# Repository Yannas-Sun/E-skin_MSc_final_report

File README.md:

# E-SKIN MSc final report companion

This repository is the evidence package for a modular electronic-skin prototype and its final MSc report. It collects the report-linked experimental records, derived analyses, hardware design evidence and selected figures needed to assess the reported communication, power and calibration results.

## Contents

- [Final report PDF](main_final.pdf)
- [Project background](#project-background)
- [System and data path](#system-and-data-path)
- [Hardware overview](#hardware-overview)
- [Core reported results](#core-reported-results)
- [Repository structure](#repository-structure)
- [Software simulation](#software-simulation)
- [Evidence and reproduction](#evidence-and-reproduction)
- [Scope limits](#scope-limits)

## Project background

The final report treats the E-SKIN prototype as a system-level scalability problem. It starts from an existing modular FSR platform and evaluates whether adding sensing modules remains practical across the complete chain: local acquisition, shared communication, host transport, power delivery and calibration.

### Research gap

Existing e-skin work often foregrounds sensing materials, array geometry or local sensor performance. The report identifies a system-level gap: the available modular prototype had not been evaluated as one connected scaling problem across data traffic, regulated power and calibration repeatability. In particular, the report needed evidence for:

- whether complete FSR data can be transported as modules are added, and whether cached change-driven DELTA frames reduce the same-rate traffic;
- whether the parallel 3.3 V supply maintains the specified voltage range as module count increases, without confusing static readings with a verified transient capacity; and
- whether a layer-wide calibration workflow reduces cell-to-cell variation and reconstructs applied whole-layer mass for separately calibrated FSR layers.

The report separates measured behaviour for N = 1–4 modules from conditional model projections beyond the measured range. The repository follows the same boundary.

### Hypotheses to be tested

The report defines the following hypotheses in its Background chapter. They are listed here as the claims the evidence package is intended to test or bound.

- **D-H1 — protocol-model agreement:** within N = 1–4, observed mean FULL packet lengths and DELTA packet lengths follow the byte budgets using the recorded mask activity, complete-frame incidence and module-update coverage. Values beyond four modules remain conditional extrapolations.
- **D-H2 — DELTA traffic reduction:** change-driven DELTA reduces same-rate packet bytes under the tested activity conditions in windows without detected sequence, cache-chain or target-update anomalies.
- **P-H1 — current prediction:** separately measured single-module currents provide a useful descriptive prediction of the tested multi-module combinations under comparable operating conditions; this is not treated as proof of a universal current-versus-count law.
- **P-H2 — voltage range:** recorded module voltages remain within the project-defined 3.3 V ± 5% band for the tested configurations. Transient delivery and fault-free operation require additional monitoring.
- **C-H1 — spatial dispersion:** with matched RAW inputs and common valid cells, per-cell multi-load fitting reduces spatial dispersion relative to two-point LINEAR or GAMMA calibration, assessed separately using CV, variance, IQR and MAD.
- **C-H2 — mass reconstruction:** per-cell calibration estimates known applied whole-layer mass, quantified with signed bias, absolute error, per-cell MAE/RMSE and non-zero-load percentage error. The report specifies no pass/fail accuracy threshold, so this remains a descriptive error assessment.
- **C-H3 — second-layer repeatability:** applying the same workflow independently to a second nominally identical FSR layer retains the FIT PRESS benefit relative to LINEAR and GAMMA under the same validation procedure. This tests independent retraining across layers, not direct transfer of one fitted model.

The reported results below show which parts are supported by the measured records and which remain model-based or unmeasured.

## System and data path

The report's layered acquisition and communication path is reproduced here for orientation.

[Open the original report flow figure](<Imperial College Individual Project Template_LaTeX/figures/data/data_path_flow.pdf>).

## Hardware overview

The sensing layer places pressure-sensitive resistive foam between opposing copper electrode layers. Orthogonal row and column electrodes form a 16 × 16 matrix; pressure changes the local resistance at each row-column intersection. The STM32 scans the matrix, buffers a complete ESKF or change-driven ESKD frame, and sends it to the Teensy bridge. The mainboard uses an external regulated 3.3 V branch for the module electronics.

The ACC board shown below is an existing prototype interface. It is retained as hardware evidence but is outside the reported FSR performance evaluation.

<table width="100%">
<tr>
<td width="50%" align="center"><br>Module stack</td>
<td width="50%" align="center"><br>Rigid mainboard</td>
</tr>
<tr>
<td width="50%" align="center"><br>Flexible FSR layer</td>
<td width="50%" align="center"><br>ACC prototype</td>
</tr>
</table>

- [Hardware overview](hardware/README.md)
- [Prototype design records](hardware/prototype/README.md)
- [Shared KiCad libraries and renderings](hardware/libraries/README.md)
- [Active and archived firmware](hardware/firmware/README.md)

## Core reported results

### Communication

- The four-module FULL stream measured 6.747828 ± 0.001148 Mbit/s at the configured 200 Hz scan rate.
- Measured FULL packet lengths matched the protocol model for N = 1–4. Mean USB rates differed from the nominal 200 Hz predictions by +0.029% to +0.125%.
- Extending the FULL model to N = 100 gives 167.7184 Mbit/s; this value is unvalidated because only four modules were measured.
- DELTA reduced same-rate packet bytes by 86.60%–88.73% in zero-load windows and by 65.10%–80.57% in five audited dynamic batches.
- The fitted zero-load ordinary-mask trend is K0(N) = 7.554189 + 0.582684N. The rolling stress projection uses K = 254.
- At 200 Hz, the modelled crossing counts are conditional planning values:

<table width="100%">
<tr>
<th align="left">Traffic model</th>
<th align="right">USB 480 Mbit/s</th>
<th align="right">HOST SPI 10 Mbit/s</th>
</tr>
<tr>
<td>FULL</td>
<td align="right">286 modules</td>
<td align="right">5 modules</td>
</tr>
<tr>
<td>DELTA, zero-load K0(N)</td>
<td align="right">464 modules</td>
<td align="right">41 modules</td>
</tr>
<tr>
<td>DELTA, rolling K = 254</td>
<td align="right">501 modules</td>
<td align="right">10 modules</td>
</tr>
</table>

Only N = 1–4 is experimentally measured. The crossing counts are extrapolations from the reported packet models and interface rates.

[Report source: transport-model validation and capacity projection](<Imperial College Individual Project Template_LaTeX/figures/data/v2_11/full_model_validation.pdf>) · [Communication data and analyses](<data scalability/README.md>)

### Power

The power experiment records static voltage, branch current and temperature readings for all 15 non-empty combinations of M0–M3 under the configured 200 Hz FULL acquisition. The four-module branch-current readings were 72.513 mA and 78.720 mA in the reported branches, and the lowest accepted module minimum was 3.236 V. These static readings do not establish transient supply capacity.

[Report source: continuous-read electrical demand](<Imperial College Individual Project Template_LaTeX/figures/power/v2_9/current_power_scaling.pdf>) · [Power data and analyses](<power scalability/README.md>)

### Calibration

FSR1 and FSR2 were calibrated in separate 22-point sweeps from 0 to 5000 g. In the FSR2 evaluation, FIT PRESS produced a 10.22% mean layer-estimate APE and 171.69 g mean per-cell MAE across 21 validation captures, with a 40.12 g zero-load estimate. The report treats these metrics as comparator- and metric-dependent.

[Report source: FSR2 load reconstruction error](<Imperial College Individual Project Template_LaTeX/figures/calibration/v2_7/fsr2_load_error_vs_load.pdf>) · [Calibration data and analyses](<Calibration scalability/README.md>)

## Repository structure

| Path | Purpose |
|---|---|
| [Calibration scalability](<Calibration scalability>) | FSR1/FSR2 training sweeps, validation captures, calibration models, figures and audits. |
| [data scalability](<data scalability>) | Canonical FULL/DELTA recordings, selected windows, communication models and figures. |
| [power scalability](<power scalability>) | Canonical electrical records, matched photographs, power analyses and figures. |
| [hardware](hardware/README.md) | Prototype design files, manufacturing exports, shared libraries, renderings and firmware. |
| [LaTeX supplementary package](<Imperial College Individual Project Template_LaTeX/figures>) | Report-linked figures and [audit evidence](<Imperial College Individual Project Template_LaTeX/audit>). |
| [README assets](README_assets) | Rendered copies of the core report result figures used by this README; the data-path rendering is stored with firmware. |
| [figure_style.py](figure_style.py) | Shared plotting-style helper retained with the evidence package. |

The complete report source and build outputs are intentionally ignored by Git. The final rendered report is available at [main_final.pdf](main_final.pdf); this repository publishes the supporting records and selected supplementary material rather than a standalone report compiler.

## Evidence and reproduction

Raw records are retained as recorded in the three scalability packages. Derived tables and figures identify their input manifests and analysis directories. Scripts use portable relative paths within the organized packages; machine-specific build products, caches, live captures and temporary review files are ignored.

The audit material records provenance and validation checks for report-linked data. It does not introduce additional experiments or replace the report's stated methods.

## Scope limits

- Communication measurements stop at four modules; larger module counts are conditional projections.
- Power results are static readings and do not establish transient supply capacity.
- Cross-module calibration, calibration transfer between layers and repeatability after reassembly were not measured.
- The ACC prototype is documented as hardware evidence but is outside the reported FSR evaluation.

## Software simulation

The early software simulator is maintained in the separate [e-skin-simulator repository](https://github.com/Yannas-Sun/e-skin-simulator). It explores module geometry, FSR and accelerometer readout, protocol traffic and visualisation before all hardware paths are complete.

The simulator is an initial design and communication tool. It is not evidence for the measured report results and is not a high-fidelity electrical, mechanical or finite-element model. Scan strategies, MCU-in-the-loop behaviour, event-driven sensing, multi-patch communication and physical validation still require further development.

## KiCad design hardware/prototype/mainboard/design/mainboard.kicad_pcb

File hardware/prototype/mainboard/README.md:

# Mainboard

The mainboard is the current four-layer rigid FR4 controller board for one sensing module. It connects two replaceable FSR layers, performs local readout and ADC conversion, provides branch power and exposes programming, test and host interfaces.

## Hardware principle

The STM32G474CETx controls the local scan. Two CD74HC4067SM multiplexers select the FSR row paths, while two MAX11633EEGT ADCs sample the column paths. The controller buffers the two 16 x 16 matrices and emits an ESKF FULL or ESKD DELTA module frame. FSR row and column signals use separate FFC connectors; the ACC connector and decoder are retained as an interface for the prototype hardware.

The module is powered through the common regulated 3.3 V branch used in the report measurements. The host bridge selects the module over HOST SPI and receives the encoded module frame.

## Hardware views

### Rendering

### Schematic

### PCB layout

### Fabricated board views

<table>
<tr>
<td><br>Front</td>
<td><br>Bottom</td>
</tr>
</table>

## Principal components

| Function | Part or record | Quantity |
|---|---|---:|
| Local controller | STM32G474CETx | 1 |
| FSR column ADC | MAX11633EEGT | 2 |
| FSR row multiplexer | CD74HC4067SM | 2 |
| ACC interface decoder | CD74HC154M96 | 1 |
| FSR row/column FFC connectors | AFC01-S16FCA-00 | 4 |
| Host connector | AFC01-S10FCA-00 | 1 |
| ACC FFC connector | AFC01-S22FCA-00 | 1 |
| Resistor arrays | EXB2HV103JV, 10 kOhm | 5 |
| Decoupling | 100 nF capacitors; 10 uF capacitor | 15; 1 |
| Status indicator | SMD LED | 1 |

The list follows the board BOM; passive values and connector references are retained in the source files.

## Design and manufacturing records

- [KiCad project](design/mainboard.kicad_pro)
- [Schematic source](design/mainboard.kicad_sch)
- [PCB source](design/mainboard.kicad_pcb)
- [SPICE netlist](design/mainboard.cir)
- [BOM](manufacturing/gerber/BOM.csv)

- [Gerber files](manufacturing/gerber)

## Component references

- [STM32G474CE datasheet](../../libraries/datasheet/MAINBOARD/MCU%20(stm32g474ce).pdf)
- [MAX11626–MAX11633 ADC datasheet](../../libraries/datasheet/MAINBOARD/ADC%20(MAX11626-MAX11633).pdf)
- [CD74HC4067 multiplexer datasheet](../../libraries/datasheet/MAINBOARD/MUX%20(cd74hc4067).pdf)
- [AFC01-S16FCA-00 connector datasheet](../../libraries/datasheet/MAINBOARD/connector%20(AFC01-S16FCA-00).PDF)
- [AFC01-S10FCA-00 connector datasheet](../../libraries/datasheet/MAINBOARD/connector%20(AFC01-S10FCA-00).PDF)

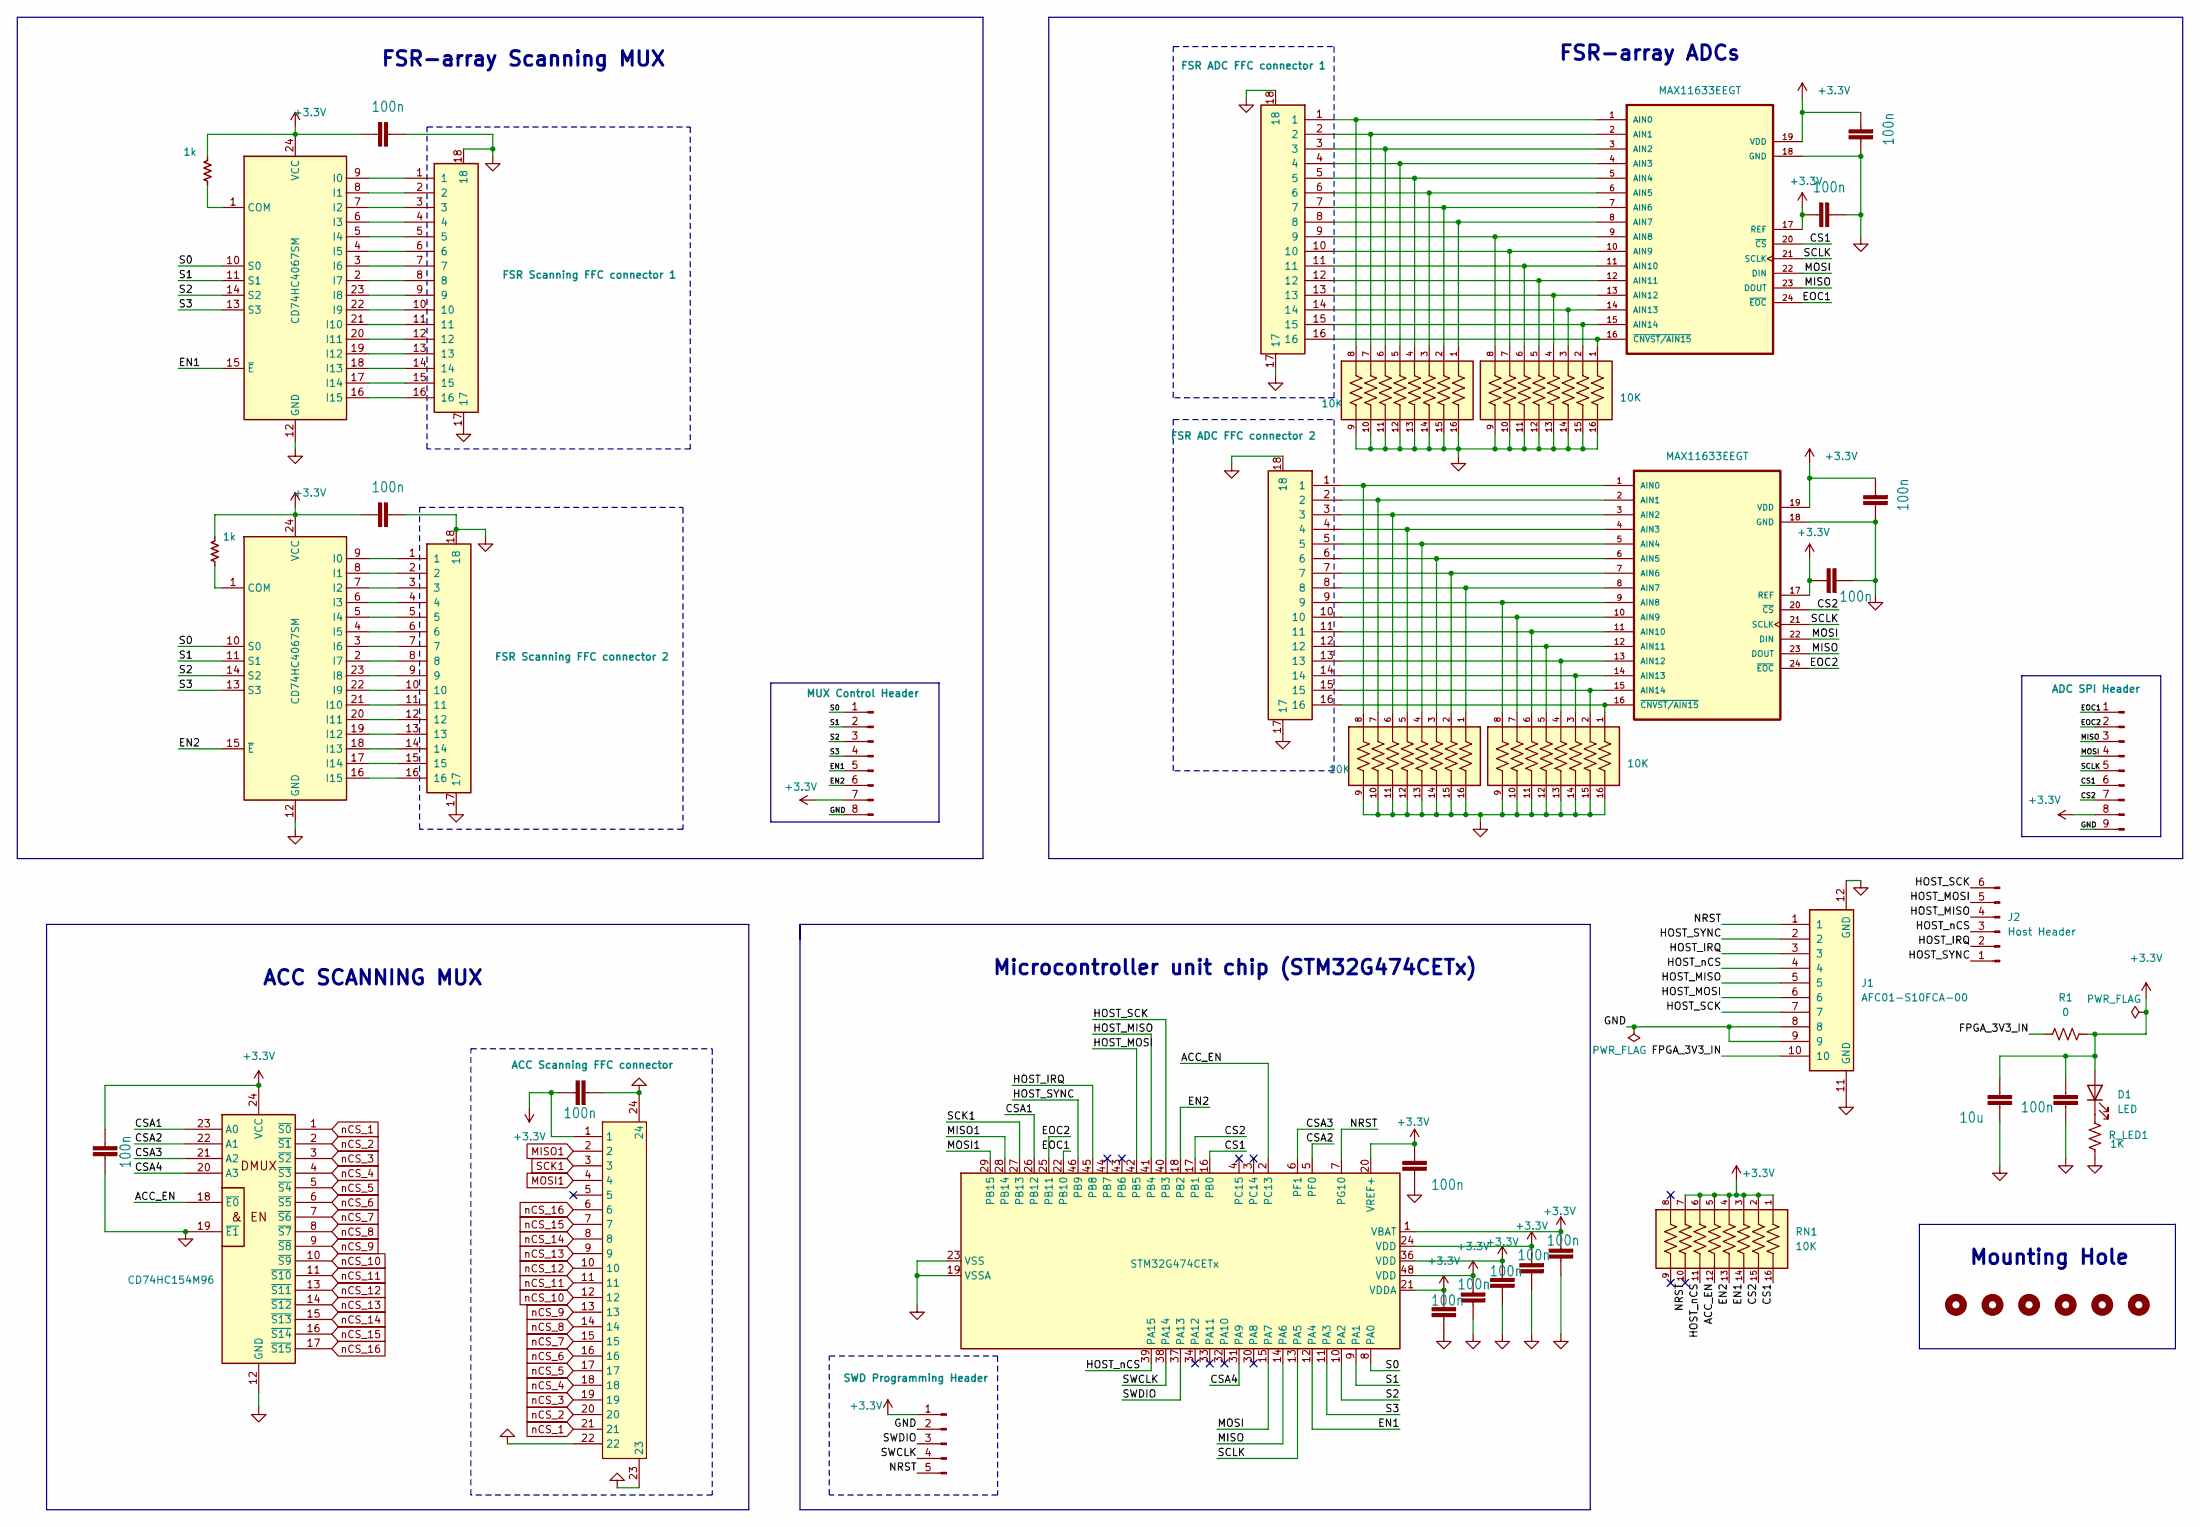
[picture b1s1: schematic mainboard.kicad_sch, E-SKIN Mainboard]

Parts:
ACC_DEC1: CD74HC154M96
ACC_FPC1: ACC Scanning FFC connector; AFC01-S22FCA-00; LCSC Part C262668
ADC_SPI_HDR1: ADC SPI Header; PinHeader_1x09_P1.27mm_Vertical
C1, C2, C5, C6, C7, C8, C9, C10, C11, C12, C13, C14, C15, C16, C17: 100n; C_0603_1608Metric
C18: 10u; C_0603_1608Metric
COL_ADC1, COL_ADC2: MAX11633EEGT
COL_FPC1: FSR ADC FFC connector 1; AFC01-S16FCA-00
COL_FPC2: FSR ADC FFC connector 2; AFC01-S16FCA-00
D1: LED; LED_0603_1608Metric
J1: AFC01-S10FCA-00
J2: Host Header; PinHeader_1x06_P1.27mm_Vertical
MCU1: STM32G474CETx; LQFP-48_7x7mm_P0.5mm
MOUNT1, MOUNT2, MOUNT3, MOUNT4, MOUNT5, MOUNT6: M3 Mounting Hole; MountingHole_3.2mm_M3
MUX_CTRL_HDR1: MUX Control Header; PinHeader_1x08_P1.27mm_Vertical
R1: 0; R_0603_1608Metric
RN1: 10K; EXB2HV103JV; PARTREV 1-Mar-20
RN2, RN3, RN4, RN5: 10K; Res-array; PARTREV 1-Mar-20
ROW_FPC1: FSR Scanning FFC connector 1; AFC01-S16FCA-00
ROW_FPC2: FSR Scanning FFC connector 2; AFC01-S16FCA-00
ROW_MUX1, ROW_MUX2: CD74HC4067SM; SSOP-24_5.3x8.2mm_P0.65mm
R_LED1: 1K; R_0603_1608Metric
R_MUX1_COM1, R_MUX2_COM1: 1k; R_0603_1608Metric
SWD_HDR1: SWD Programming Header; PinHeader_1x05_P1.27mm_Vertical

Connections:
+3.3V: ACC_DEC1.24 (VCC), ACC_FPC1.1, ADC_SPI_HDR1.8, C1.2, C2.1, C5.2, C6.2, C7.2, C8.1, C9.2, C10.2, C11.2, C12.2, C13.2, C14.2, C15.2, C16.2, C17.2, C18.2, COL_ADC1.17 (REF), COL_ADC1.19 (VDD), COL_ADC2.17 (REF), COL_ADC2.19 (VDD), D1.2 (A), MCU1.1 (VBAT), MCU1.20 (VREF+), MCU1.21 (VDDA), MCU1.24 (VDD), MCU1.36 (VDD), MCU1.48 (VDD), MUX_CTRL_HDR1.7, R1.2, RN1.1, RN1.2, RN1.3, RN1.4, RN1.5, RN1.6, RN1.7, ROW_MUX1.24 (VCC), ROW_MUX2.24 (VCC), R_MUX1_COM1.1, R_MUX2_COM1.1, SWD_HDR1.1; also elsewhere on the board
/ACC_EN: ACC_DEC1.18 (~E0), MCU1.2 (PC13), RN1.12; also elsewhere on the board
/CS1: ADC_SPI_HDR1.6, COL_ADC1.20 (~CS), MCU1.16 (PB0), RN1.16; also elsewhere on the board
/CS2: ADC_SPI_HDR1.7, COL_ADC2.20 (~CS), MCU1.17 (PB1), RN1.15; also elsewhere on the board
/CSA1: ACC_DEC1.23 (A0), MCU1.26 (PB12); also elsewhere on the board
/CSA2: ACC_DEC1.22 (A1), MCU1.5 (PF0); also elsewhere on the board
/CSA3: ACC_DEC1.21 (A2), MCU1.6 (PF1); also elsewhere on the board
/CSA4: ACC_DEC1.20 (A3), MCU1.31 (PA9); also elsewhere on the board
/EN1: MCU1.12 (PA4), MUX_CTRL_HDR1.5, RN1.14, ROW_MUX1.15 (~E); also elsewhere on the board
/EN2: MCU1.18 (PB2), MUX_CTRL_HDR1.6, RN1.13, ROW_MUX2.15 (~E); also elsewhere on the board
/EOC1: ADC_SPI_HDR1.1, COL_ADC1.24 (~EOC), MCU1.22 (PB10); also elsewhere on the board
/EOC2: ADC_SPI_HDR1.2, COL_ADC2.24 (~EOC), MCU1.25 (PB11); also elsewhere on the board
/FPGA_3V3_IN: J1.10, R1.1
/HOST_IRQ: J1.3, J2.2, MCU1.45 (PB8); also elsewhere on the board
/HOST_MISO: J1.5, J2.4, MCU1.41 (PB4); also elsewhere on the board
/HOST_MOSI: J1.6, J2.5, MCU1.42 (PB5); also elsewhere on the board
/HOST_SCK: J1.7, J2.6, MCU1.40 (PB3); also elsewhere on the board
/HOST_SYNC: J1.2, J2.1, MCU1.46 (PB9); also elsewhere on the board
/HOST_nCS: J1.4, J2.3, MCU1.39 (PA15), RN1.11; also elsewhere on the board
/MISO: ADC_SPI_HDR1.3, COL_ADC1.23 (DOUT), COL_ADC2.23 (DOUT), MCU1.14 (PA6); also elsewhere on the board
/MOSI: ADC_SPI_HDR1.4, COL_ADC1.22 (DIN), COL_ADC2.22 (DIN), MCU1.15 (PA7); also elsewhere on the board
/NRST: J1.1, MCU1.7 (PG10), RN1.10, SWD_HDR1.5; also elsewhere on the board
/S0: MCU1.8 (PA0), MUX_CTRL_HDR1.1, ROW_MUX1.10 (S0), ROW_MUX2.10 (S0); also elsewhere on the board
/S1: MCU1.9 (PA1), MUX_CTRL_HDR1.2, ROW_MUX1.11 (S1), ROW_MUX2.11 (S1); also elsewhere on the board
/S2: MCU1.10 (PA2), MUX_CTRL_HDR1.3, ROW_MUX1.14 (S2), ROW_MUX2.14 (S2); also elsewhere on the board
/S3: MCU1.11 (PA3), MUX_CTRL_HDR1.4, ROW_MUX1.13 (S3), ROW_MUX2.13 (S3); also elsewhere on the board
/SCLK: ADC_SPI_HDR1.5, COL_ADC1.21 (SCLK), COL_ADC2.21 (SCLK), MCU1.13 (PA5); also elsewhere on the board
/SWCLK: MCU1.38 (PA14), SWD_HDR1.4; also elsewhere on the board
/SWDIO: MCU1.37 (PA13), SWD_HDR1.3; also elsewhere on the board
GND: ACC_DEC1.12 (GND), ACC_DEC1.19 (~E1), ACC_FPC1.22, ACC_FPC1.23, ACC_FPC1.24, ADC_SPI_HDR1.9, C1.1, C2.2, C5.1, C6.1, C7.1, C8.2, C9.1, C10.1, C11.1, C12.1, C13.1, C14.1, C15.1, C16.1, C17.1, C18.1, COL_ADC1.18 (GND), COL_ADC2.18 (GND), COL_FPC1.17, COL_FPC1.18, COL_FPC2.17, COL_FPC2.18, J1.8, J1.9, J1.11 (GND), J1.12 (GND), MCU1.19 (VSSA), MCU1.23 (VSS), MCU1.35 (VSS), MCU1.47 (VSS), MUX_CTRL_HDR1.8, RN2.9, RN2.10, RN2.11, RN2.12, RN2.13, RN2.14, RN2.15, RN2.16, RN3.9, RN3.10, RN3.11, RN3.12, RN3.13, RN3.14, RN3.15, RN3.16, RN4.9, RN4.10, RN4.11, RN4.12, RN4.13, RN4.14, RN4.15, RN4.16, RN5.9, RN5.10, RN5.11, RN5.12, RN5.13, RN5.14, RN5.15, RN5.16, ROW_FPC1.17, ROW_FPC1.18, ROW_FPC2.17, ROW_FPC2.18, ROW_MUX1.12 (GND), ROW_MUX2.12 (GND), R_LED1.2, SWD_HDR1.2; also elsewhere on the board
MISO1: ACC_FPC1.2; also elsewhere on the board
MOSI1: ACC_FPC1.4; also elsewhere on the board
unnamed: COL_ADC1.1 (AIN0), COL_FPC1.1, RN3.8
unnamed: COL_ADC1.2 (AIN1), COL_FPC1.2, RN3.7
unnamed: COL_ADC1.3 (AIN2), COL_FPC1.3, RN3.6
unnamed: COL_ADC1.4 (AIN3), COL_FPC1.4, RN3.5
unnamed: COL_ADC1.5 (AIN4), COL_FPC1.5, RN3.4
unnamed: COL_ADC1.6 (AIN5), COL_FPC1.6, RN3.3
unnamed: COL_ADC1.7 (AIN6), COL_FPC1.7, RN3.2
unnamed: COL_ADC1.8 (AIN7), COL_FPC1.8, RN3.1
unnamed: COL_ADC1.9 (AIN8), COL_FPC1.9, RN2.8
unnamed: COL_ADC1.10 (AIN9), COL_FPC1.10, RN2.7
unnamed: COL_ADC1.11 (AIN10), COL_FPC1.11, RN2.6
unnamed: COL_ADC1.12 (AIN11), COL_FPC1.12, RN2.5
unnamed: COL_ADC1.13 (AIN12), COL_FPC1.13, RN2.4
unnamed: COL_ADC1.14 (AIN13), COL_FPC1.14, RN2.3
unnamed: COL_ADC1.15 (AIN14), COL_FPC1.15, RN2.2
unnamed: COL_ADC1.16 (~CNVST/AIN15), COL_FPC1.16, RN2.1
unnamed: COL_ADC2.1 (AIN0), COL_FPC2.1, RN4.8
unnamed: COL_ADC2.2 (AIN1), COL_FPC2.2, RN4.7
unnamed: COL_ADC2.3 (AIN2), COL_FPC2.3, RN4.6
unnamed: COL_ADC2.4 (AIN3), COL_FPC2.4, RN4.5
unnamed: COL_ADC2.5 (AIN4), COL_FPC2.5, RN4.4
unnamed: COL_ADC2.6 (AIN5), COL_FPC2.6, RN4.3
unnamed: COL_ADC2.7 (AIN6), COL_FPC2.7, RN4.2
unnamed: COL_ADC2.8 (AIN7), COL_FPC2.8, RN4.1
unnamed: COL_ADC2.9 (AIN8), COL_FPC2.9, RN5.8
unnamed: COL_ADC2.10 (AIN9), COL_FPC2.10, RN5.7
unnamed: COL_ADC2.11 (AIN10), COL_FPC2.11, RN5.6
unnamed: COL_ADC2.12 (AIN11), COL_FPC2.12, RN5.5
unnamed: COL_ADC2.13 (AIN12), COL_FPC2.13, RN5.4
unnamed: COL_ADC2.14 (AIN13), COL_FPC2.14, RN5.3
unnamed: COL_ADC2.15 (AIN14), COL_FPC2.15, RN5.2
unnamed: COL_ADC2.16 (~CNVST/AIN15), COL_FPC2.16, RN5.1
unnamed: D1.1 (K), R_LED1.1
unnamed: ROW_MUX1.1 (COM), R_MUX1_COM1.2
unnamed: ROW_FPC1.1, ROW_MUX1.9 (I0)
unnamed: ROW_FPC1.2, ROW_MUX1.8 (I1)
unnamed: ROW_FPC1.3, ROW_MUX1.7 (I2)
unnamed: ROW_FPC1.4, ROW_MUX1.6 (I3)
unnamed: ROW_FPC1.5, ROW_MUX1.5 (I4)
unnamed: ROW_FPC1.6, ROW_MUX1.4 (I5)
unnamed: ROW_FPC1.7, ROW_MUX1.3 (I6)
unnamed: ROW_FPC1.8, ROW_MUX1.2 (I7)
unnamed: ROW_FPC1.9, ROW_MUX1.23 (I8)
unnamed: ROW_FPC1.10, ROW_MUX1.22 (I9)
unnamed: ROW_FPC1.11, ROW_MUX1.21 (I10)
unnamed: ROW_FPC1.12, ROW_MUX1.20 (I11)
unnamed: ROW_FPC1.13, ROW_MUX1.19 (I12)
unnamed: ROW_FPC1.14, ROW_MUX1.18 (I13)
unnamed: ROW_FPC1.15, ROW_MUX1.17 (I14)
unnamed: ROW_FPC1.16, ROW_MUX1.16 (I15)
unnamed: ROW_MUX2.1 (COM), R_MUX2_COM1.2
unnamed: ROW_FPC2.1, ROW_MUX2.9 (I0)
unnamed: ROW_FPC2.2, ROW_MUX2.8 (I1)
unnamed: ROW_FPC2.3, ROW_MUX2.7 (I2)
unnamed: ROW_FPC2.4, ROW_MUX2.6 (I3)
unnamed: ROW_FPC2.5, ROW_MUX2.5 (I4)
unnamed: ROW_FPC2.6, ROW_MUX2.4 (I5)
unnamed: ROW_FPC2.7, ROW_MUX2.3 (I6)
unnamed: ROW_FPC2.8, ROW_MUX2.2 (I7)
unnamed: ROW_FPC2.9, ROW_MUX2.23 (I8)
unnamed: ROW_FPC2.10, ROW_MUX2.22 (I9)
unnamed: ROW_FPC2.11, ROW_MUX2.21 (I10)
unnamed: ROW_FPC2.12, ROW_MUX2.20 (I11)
unnamed: ROW_FPC2.13, ROW_MUX2.19 (I12)
unnamed: ROW_FPC2.14, ROW_MUX2.18 (I13)
unnamed: ROW_FPC2.15, ROW_MUX2.17 (I14)
unnamed: ROW_FPC2.16, ROW_MUX2.16 (I15)
SCK1: ACC_FPC1.3; also elsewhere on the board
nCS_1: ACC_DEC1.1 (~S0), ACC_FPC1.21
nCS_2: ACC_DEC1.2 (~S1), ACC_FPC1.20
nCS_3: ACC_DEC1.3 (~S2), ACC_FPC1.19
nCS_4: ACC_DEC1.4 (~S3), ACC_FPC1.18
nCS_5: ACC_DEC1.5 (~S4), ACC_FPC1.17
nCS_6: ACC_DEC1.6 (~S5), ACC_FPC1.16
nCS_7: ACC_DEC1.7 (~S6), ACC_FPC1.15
nCS_8: ACC_DEC1.8 (~S7), ACC_FPC1.14
nCS_9: ACC_DEC1.9 (~S8), ACC_FPC1.13
nCS_10: ACC_DEC1.10 (~S9), ACC_FPC1.12
nCS_11: ACC_DEC1.11 (~S10), ACC_FPC1.11
nCS_12: ACC_DEC1.13 (~S11), ACC_FPC1.10
nCS_13: ACC_DEC1.14 (~S12), ACC_FPC1.9
nCS_14: ACC_DEC1.15 (~S13), ACC_FPC1.8
nCS_15: ACC_DEC1.16 (~S14), ACC_FPC1.7
nCS_16: ACC_DEC1.17 (~S15), ACC_FPC1.6

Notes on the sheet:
FSR-array ADCs
ACC SCANNING MUX
Microcontroller unit chip (STM32G474CETx)
FSR-array Scanning MUX
Mounting Hole

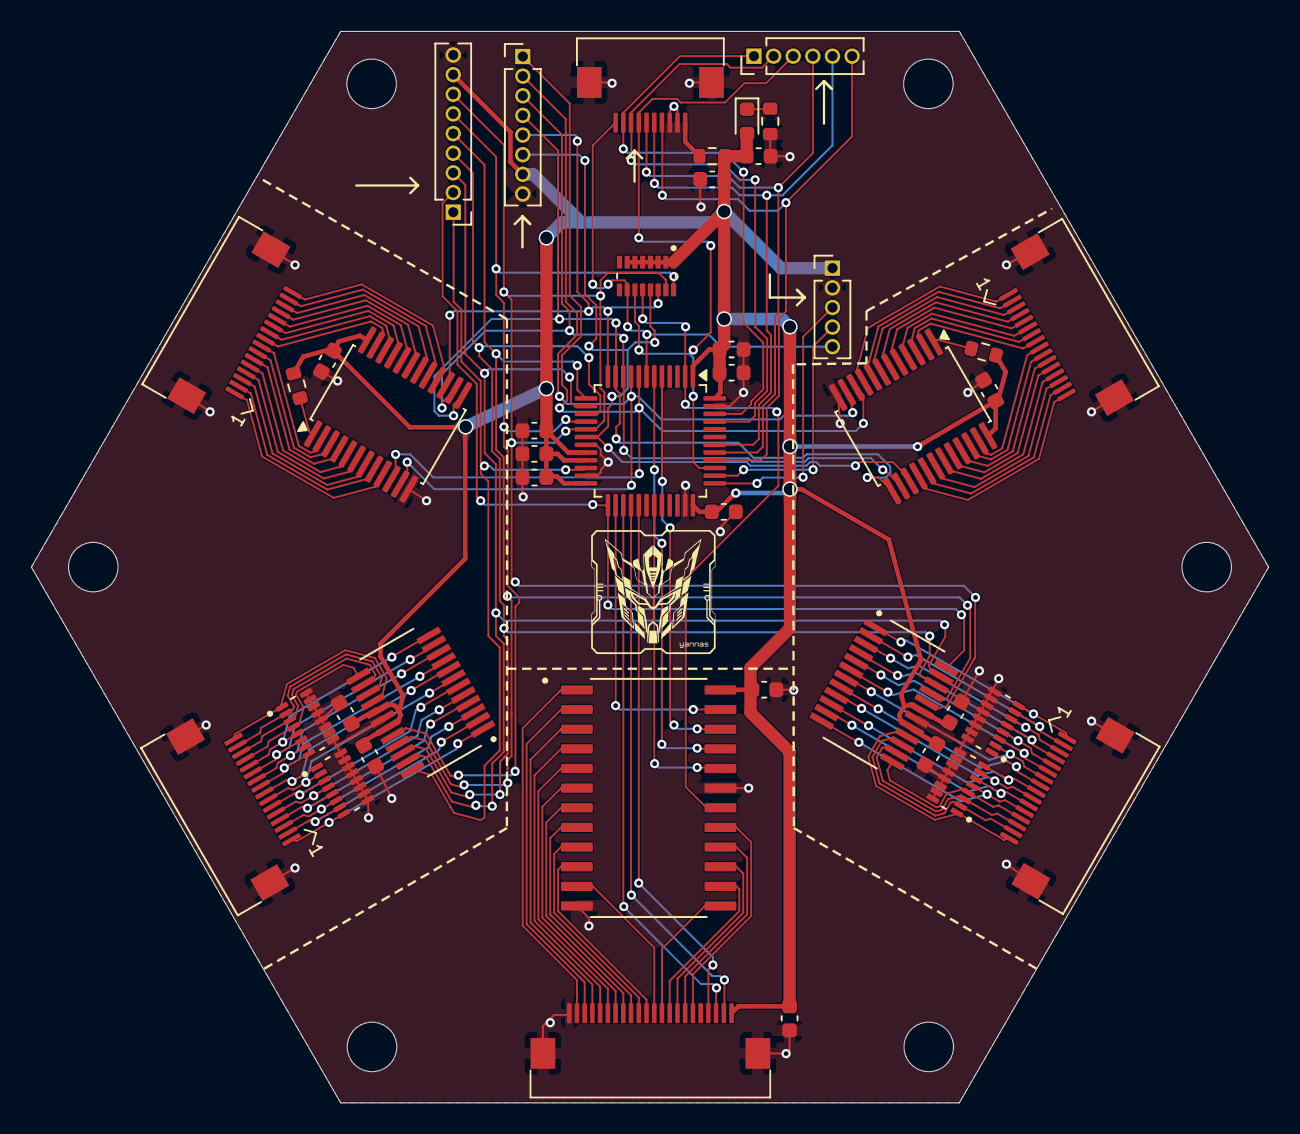
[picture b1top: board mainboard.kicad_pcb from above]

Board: 4 copper layers, 80.0 x 69.3 mm, 48 parts (0 on the bottom side), 116 nets.

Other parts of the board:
MCU: STM32G474CETx; LQFP-48_7x7mm_P0.5mm

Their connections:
+3.3V: MCU.1 (VBAT), MCU.20 (VREF+), MCU.21 (VDDA), MCU.24 (VDD), MCU.36 (VDD), MCU.48 (VDD); also elsewhere on the board
/ACC_EN: MCU.2 (PC13); also elsewhere on the board
/CS1: MCU.16 (PB0); also elsewhere on the board
/CS2: MCU.17 (PB1); also elsewhere on the board
/CSA1: MCU.26 (PB12); also elsewhere on the board
/CSA2: MCU.5 (PF0); also elsewhere on the board
/CSA3: MCU.6 (PF1); also elsewhere on the board
/CSA4: MCU.31 (PA9); also elsewhere on the board
/EN1: MCU.12 (PA4); also elsewhere on the board
/EN2: MCU.18 (PB2); also elsewhere on the board
/EOC1: MCU.22 (PB10); also elsewhere on the board
/EOC2: MCU.25 (PB11); also elsewhere on the board
/HOST_IRQ: MCU.45 (PB8); also elsewhere on the board
/HOST_MISO: MCU.41 (PB4); also elsewhere on the board
/HOST_MOSI: MCU.42 (PB5); also elsewhere on the board
/HOST_SCK: MCU.40 (PB3); also elsewhere on the board
/HOST_SYNC: MCU.46 (PB9); also elsewhere on the board
/HOST_nCS: MCU.39 (PA15); also elsewhere on the board
/MISO: MCU.14 (PA6); also elsewhere on the board
/MOSI: MCU.15 (PA7); also elsewhere on the board
/NRST: MCU.7 (PG10); also elsewhere on the board
/S0: MCU.8 (PA0); also elsewhere on the board
/S1: MCU.9 (PA1); also elsewhere on the board
/S2: MCU.10 (PA2); also elsewhere on the board
/S3: MCU.11 (PA3); also elsewhere on the board
/SCLK: MCU.13 (PA5); also elsewhere on the board
/SWCLK: MCU.38 (PA14); also elsewhere on the board
/SWDIO: MCU.37 (PA13); also elsewhere on the board
GND: MCU.19 (VSSA), MCU.23 (VSS), MCU.35 (VSS), MCU.47 (VSS); also elsewhere on the board
MISO1: MCU.28 (PB14); also elsewhere on the board
MOSI1: MCU.29 (PB15); also elsewhere on the board
SCK1: MCU.27 (PB13); also elsewhere on the board

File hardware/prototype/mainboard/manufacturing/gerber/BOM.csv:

Reference,Value,Datasheet,Footprint,Qty,Source
J1,AFC01-S10FCA-00,../../../../libraries/datasheet/MAINBOARD/connector (AFC01-S10FCA-00).PDF,000:AFC01-S10FCA-00,1,LCSC
ROW_FPC2,FSR Scanning FFC connector 2,${KIPRJMOD}/../../../DATA SHEET/connector (AFC01-S16FCA-00).PDF,000:AFC01-S16FCA-00,1,LCSC
ROW_FPC1,FSR Scanning FFC connector 1,${KIPRJMOD}/../../../DATA SHEET/connector (AFC01-S16FCA-00).PDF,000:AFC01-S16FCA-00,1,LCSC
COL_FPC2,FSR ADC FFC connector 2,${KIPRJMOD}/../../../DATA SHEET/connector (AFC01-S16FCA-00).PDF,000:AFC01-S16FCA-00,1,LCSC
COL_FPC1,FSR ADC FFC connector 1,${KIPRJMOD}/../../../DATA SHEET/connector (AFC01-S16FCA-00).PDF,000:AFC01-S16FCA-00,1,LCSC
ACC_FPC1,ACC Scanning FFC connector,https://lcsc.com/product-detail/Others_JUSHUO-AFC01-S22FCA-0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,000:AFC01-S22FCA-00,1,LCSC
ACC_DEC1,CD74HC154M96,https://www.ti.com/lit/gpn/CD74HCT154,000:CD74HC154M96,1,LCSC
"COL_ADC1,COL_ADC2",MAX11633EEGT,,000:MAX11633EEGT,2,Digikey
"RN1,RN2,RN3,RN4,RN5",10K,,000:EXB2HV103JV,5,LCSC
C18,10u,,Capacitor_SMD:C_0603_1608Metric,1,LCSC
"C1,C2,C5,C6,C7,C8,C9,C10,C11,C12,C13,C14,C15,C16,C17",100n,,Capacitor_SMD:C_0603_1608Metric,15,LCSC
D1,LED,,LED_SMD:LED_0603_1608Metric,1,LCSC
MCU1,STM32G474CETx,https://www.st.com/resource/en/datasheet/stm32g474ce.pdf,Package_QFP:LQFP-48_7x7mm_P0.5mm,1,Digikey
"ROW_MUX1,ROW_MUX2",CD74HC4067SM,http://www.ti.com/lit/ds/symlink/cd74hc4067.pdf,Package_SO:SSOP-24_5.3x8.2mm_P0.65mm,2,LCSC
"R_MUX1_COM1,R_MUX2_COM1",1k,,Resistor_SMD:R_0603_1608Metric,2,LCSC
R_LED1,1K,,Resistor_SMD:R_0603_1608Metric,1,LCSC
R1,0,,Resistor_SMD:R_0603_1608Metric,1,LCSC

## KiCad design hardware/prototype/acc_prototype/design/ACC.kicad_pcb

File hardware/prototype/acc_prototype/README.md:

# ACC prototype interface

This directory contains the flexible accelerometer interface retained as a hardware prototype record. It is outside the reported FSR performance evaluation.

## Hardware principle

The ACC layer places accelerometer devices on a flexible carrier and routes their local logic and supply connections to an FFC tail. The current manufacturing BOM lists nine LIS2DH12TR accelerometers. Each sensor is paired with local 100 nF and 1 uF decoupling, and SN74LVC1G32DCKR logic gates provide the interface logic shown in the unit schematics.

The mainboard ACC connector and CD74HC154M96 decoder provide the module-side interface. These records document the existing prototype; no ACC measurements are included in the report results.

## Hardware views

### Rendering

### Schematic

### PCB layout

### Fabricated board views

<table>
<tr>
<td><br>Front</td>
<td><br>Bottom</td>
</tr>
</table>

## Principal components

| Function | Part or record | Quantity |
|---|---|---:|
| Accelerometer | LIS2DH12TR | 9 |
| Interface logic | SN74LVC1G32DCKR | 9 |
| Local decoupling | 100 nF capacitors | 9 |
| Local decoupling | 1 uF capacitors | 9 |
| Flexible tail connector | AFC01-S22FCA-00_FPC_TAIL | 1 |

The design directory also retains LIS2DH and LIS3DH unit-level schematic records. The manufacturing BOM identifies LIS2DH12TR as the populated accelerometer.

## Design and manufacturing records

- [KiCad project](design/ACC.kicad_pro)
- [ACC schematic source](design/ACC.kicad_sch)
- [PCB source](design/ACC.kicad_pcb)
- [LIS2DH unit schematic](design/LIS2DH_unit1.kicad_sch)
- [LIS3DH unit schematic](design/LIS3DH_unit1.kicad_sch)
- [BOM](manufacturing/gerber/ACC.csv)
- [Gerber archive](manufacturing/gerber.zip)
- [Gerber files](manufacturing/gerber)

## Component references

- [LIS2DH12 datasheet](../../libraries/datasheet/ACC/ACC%20(LIS2DH12).pdf)
- [LIS3DH datasheet](../../libraries/datasheet/ACC/ACC%20(LIS3DH).pdf)
- [SN74LVC1G32DCKR datasheet](../../libraries/datasheet/ACC/OR%20GATE%20(SN74LVC1G32DCKR).pdf)
- [AFC01-S22FCA-00 connector datasheet](../../libraries/datasheet/ACC/CONNECTOR%20(AFC01-S22FCA-00).pdf)

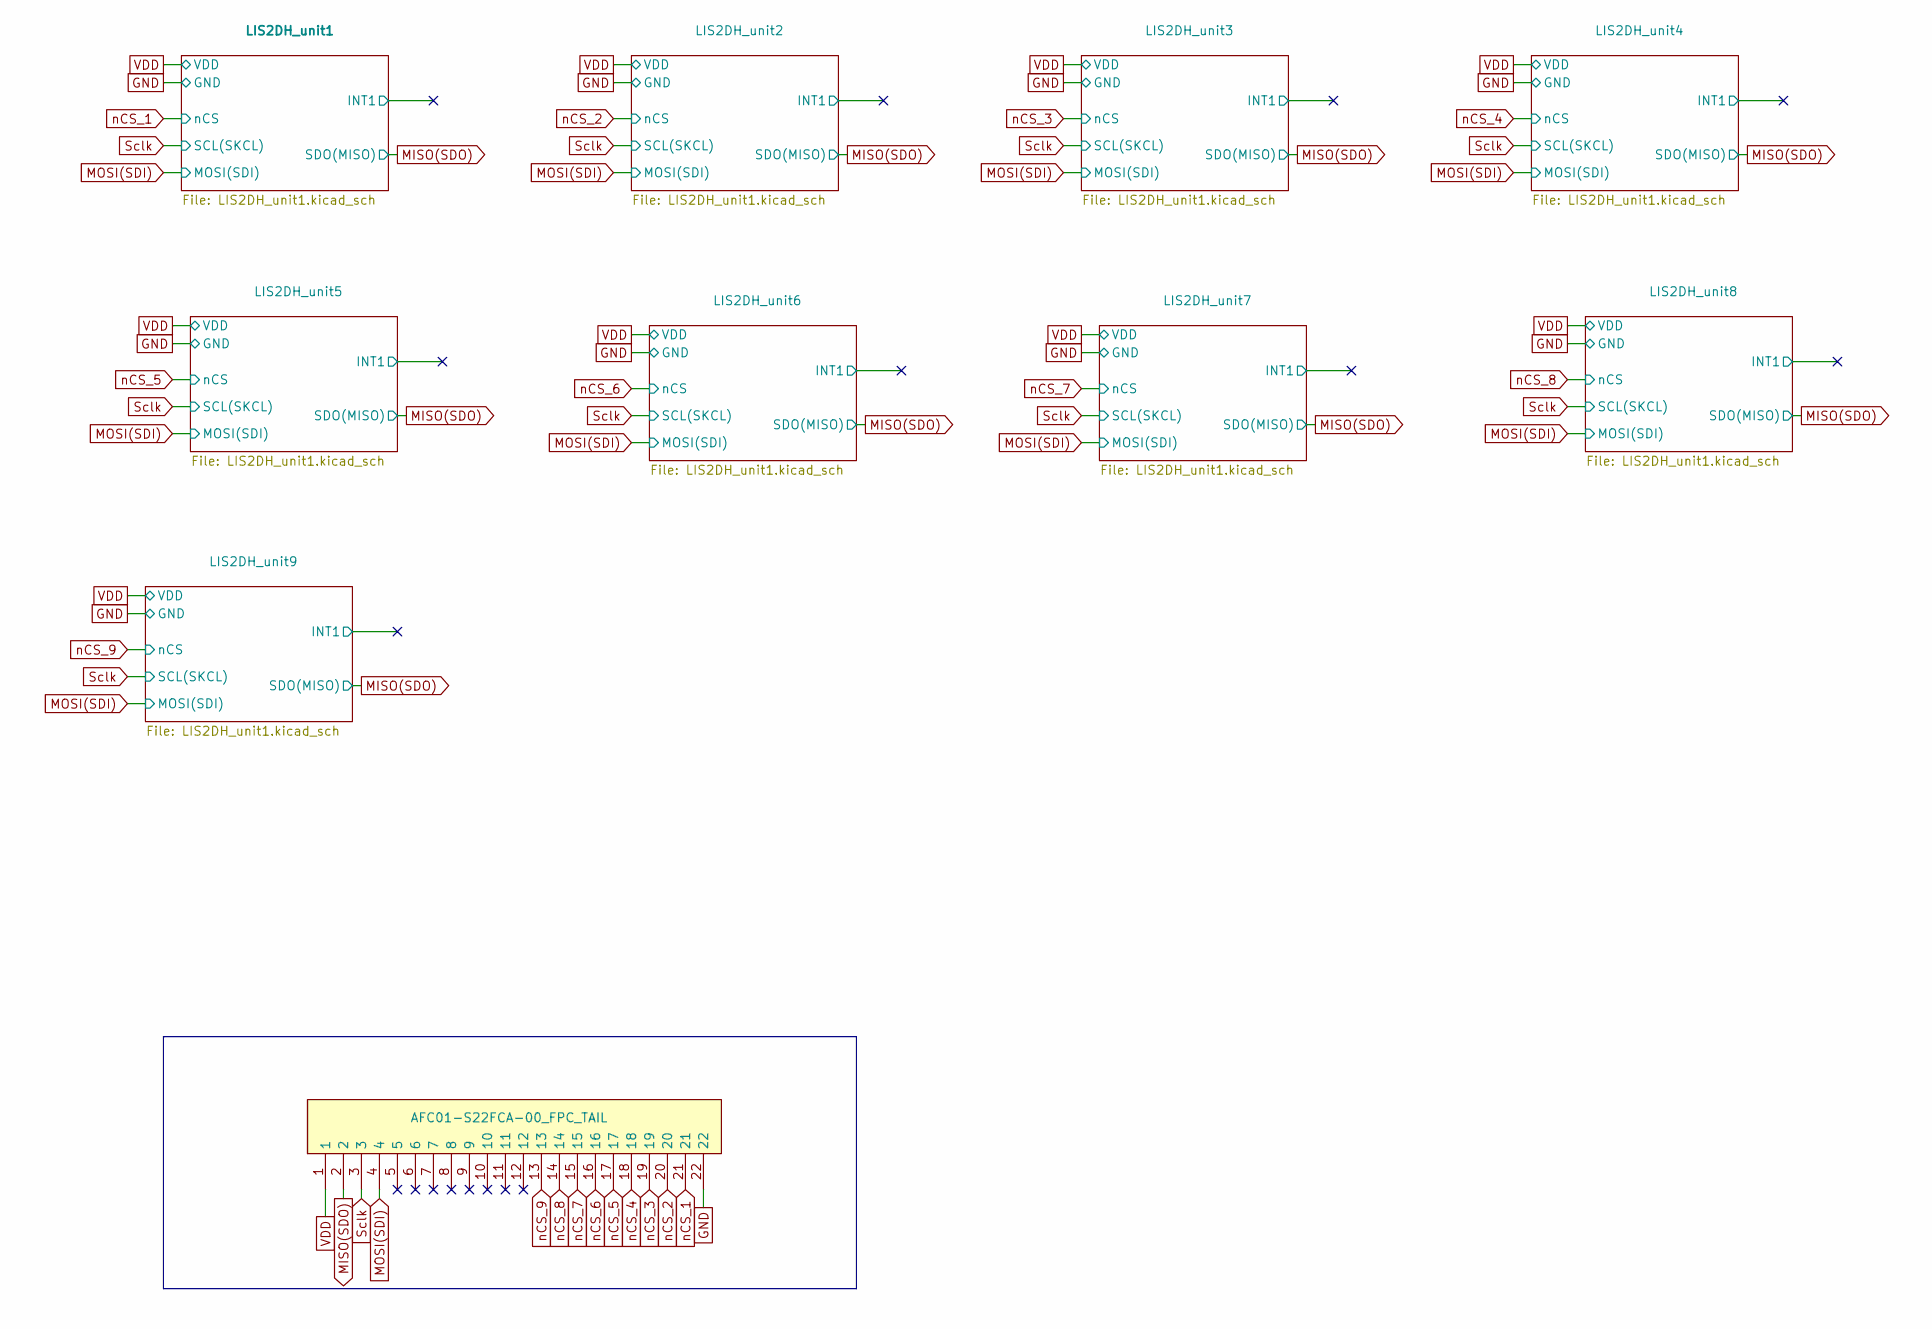
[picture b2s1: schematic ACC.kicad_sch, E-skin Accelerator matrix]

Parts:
FFC_connector1: AFC01-S22FCA-00_FPC_TAIL; LCSC Part C262668

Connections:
GND: FFC_connector1.22; also elsewhere on the board
MISO(SDO): FFC_connector1.2; also elsewhere on the board
MOSI(SDI): FFC_connector1.4; also elsewhere on the board
Sclk: FFC_connector1.3; also elsewhere on the board
VDD: FFC_connector1.1; also elsewhere on the board
nCS_1: FFC_connector1.21; also elsewhere on the board
nCS_2: FFC_connector1.20; also elsewhere on the board
nCS_3: FFC_connector1.19; also elsewhere on the board
nCS_4: FFC_connector1.18; also elsewhere on the board
nCS_5: FFC_connector1.17; also elsewhere on the board
nCS_6: FFC_connector1.16; also elsewhere on the board
nCS_7: FFC_connector1.15; also elsewhere on the board
nCS_8: FFC_connector1.14; also elsewhere on the board
nCS_9: FFC_connector1.13; also elsewhere on the board
